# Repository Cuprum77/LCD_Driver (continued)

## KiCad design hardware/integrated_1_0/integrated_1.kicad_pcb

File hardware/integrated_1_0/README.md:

# Integrated Solution rev 1.0

## DO NOT REPRODUCE, CRITICAL ERRORS IN DESIGN

This design features a nasty error where the internal and IO power rails were accidentally swapped. Do not reproduce this design. A new revision is in the works.

## Introduction

This is a PCB that integrates everything needed to drive the display. It is designed to sit on the back of the display without interfering with the display frame. It is specifically designed for the pinout of the newer non-standard displays that have come out of China in the recent years. Specifically those that support the RGB666 interface.

This design utilizes a Spartan 6 FPGA to drive the display. This was chosen over dedicated ASICs due to cost and adaptability. This should allow me to add features such as a splash screen or other custom features that are not possible with a dedicated ASIC.

## Features
- Spartan 6 FPGA [^1]
- DVI Input [^2]
- RP2040 microcontroller
- USB-C [^3] [^4]
- Backlight driver with dimming control
- LCD connector

## LCD Connector

The LCD connector itself is a ZIF 40 pin 0.5mm pitch connector.
The following pinout is in use, with some pins being possible to reconfigure in the FPGA:

TO BE ADDED

[^1]: XC6SLX9-TQG144
[^2]: The DVI input is over a HDMI-like connector. This is due to licensing issues with the HDMI standard that I cannot afford to pay for. Any reference to HDMI in this project is purely for the sake of simplicity and is not meant to imply that this project is HDMI compatible.
[^3]: Does not support PD.
[^4]: Limited to USB 1.1 speeds. This is limited by the RP2040 which handles the USB interface.

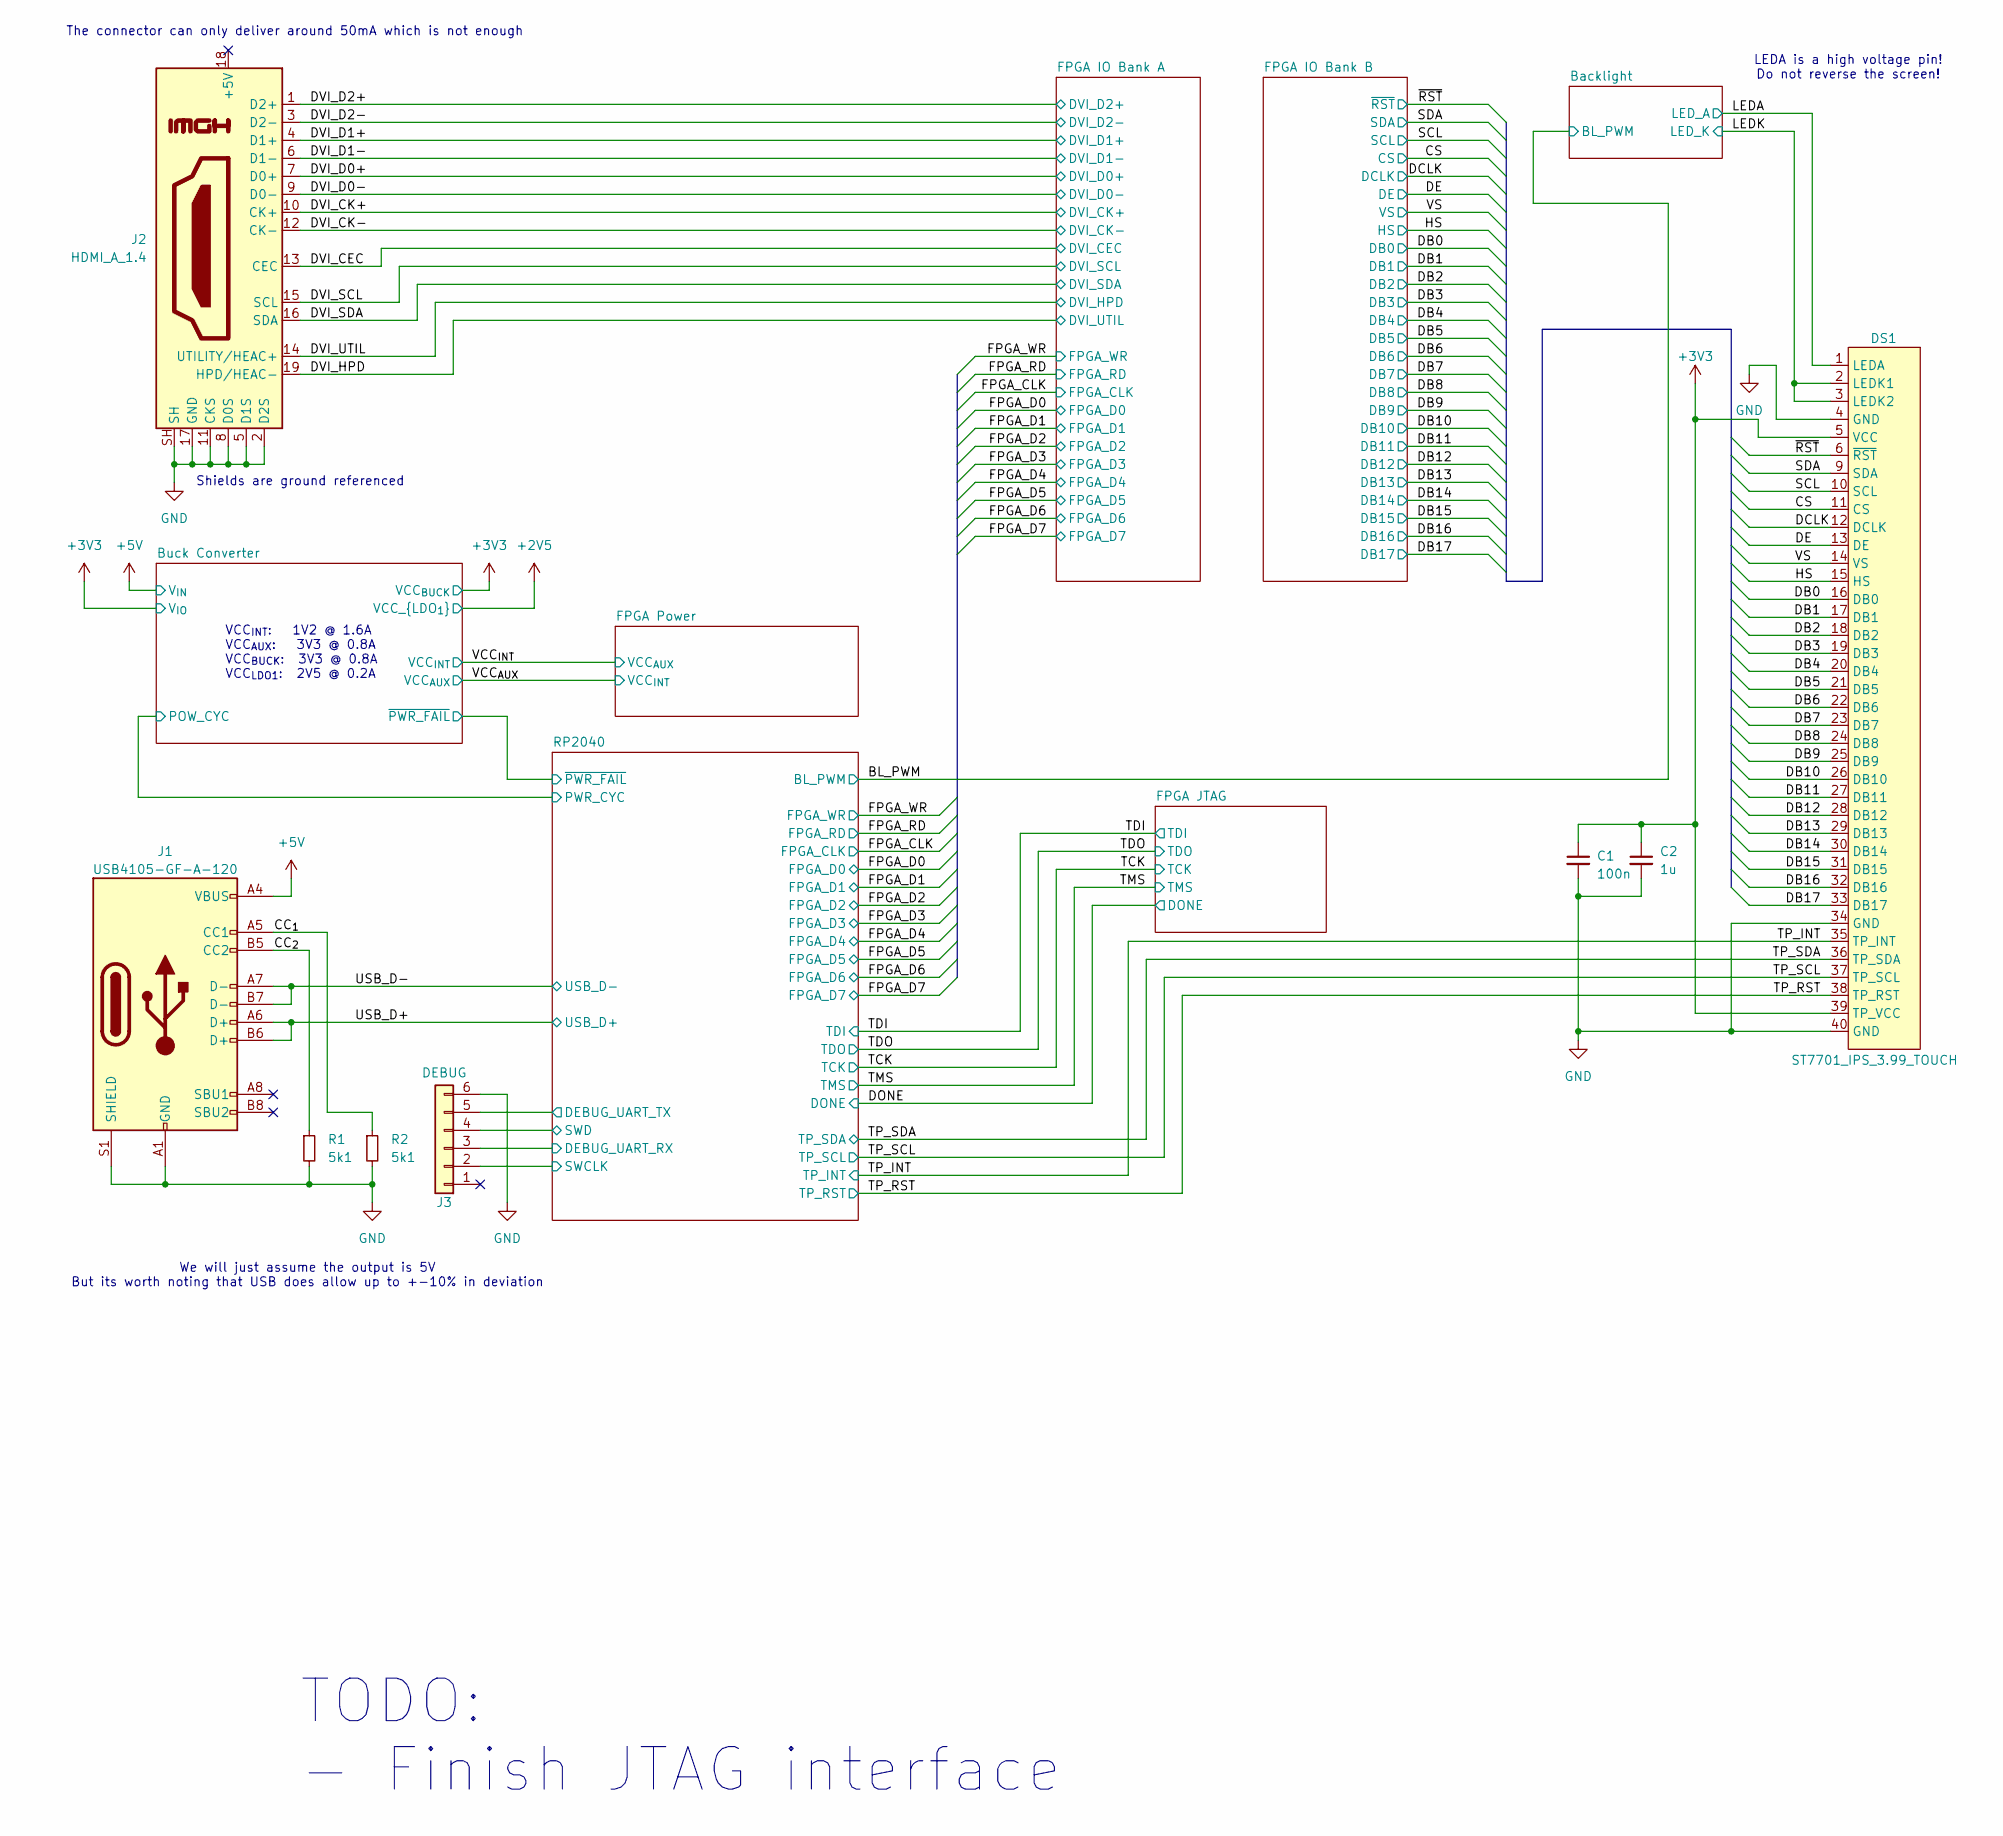
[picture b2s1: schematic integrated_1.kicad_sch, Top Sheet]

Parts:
C1: 100n; C_0402_1005Metric
C2: 1u; C_0402_1005Metric
DS1: ST7701_IPS_3.99_TOUCH; GCT_FFC2B35-40-G_REVA2_INV
J1: USB4105-GF-A-120; CONN_217182-0001_MOL
J2: HDMI_A_1.4; MOLEX_476591102
J3: DEBUG; Paw-Connect_RevB_TC2030-IDC-NL_2x03_P1.27mm_Vertical
R1, R2: 5k1; R_0402_1005Metric

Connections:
+3V3: C1.1, C2.1, DS1.5 (VCC), DS1.39 (TP_VCC); also elsewhere on the board
+5V: J1.A4 (VBUS), J1.A9 (VBUS), J1.B4 (VBUS), J1.B9 (VBUS); also elsewhere on the board
/CC_{1}: J1.A5 (CC1), R2.1
/CC_{2}: J1.B5 (CC2), R1.1
/CS: DS1.11 (CS); also elsewhere on the board
/DB0: DS1.16 (DB0); also elsewhere on the board
/DB1: DS1.17 (DB1); also elsewhere on the board
/DB2: DS1.18 (DB2); also elsewhere on the board
/DB3: DS1.19 (DB3); also elsewhere on the board
/DB4: DS1.20 (DB4); also elsewhere on the board
/DB5: DS1.21 (DB5); also elsewhere on the board
/DB6: DS1.22 (DB6); also elsewhere on the board
/DB7: DS1.23 (DB7); also elsewhere on the board
/DB8: DS1.24 (DB8); also elsewhere on the board
/DB9: DS1.25 (DB9); also elsewhere on the board
/DB10: DS1.26 (DB10); also elsewhere on the board
/DB11: DS1.27 (DB11); also elsewhere on the board
/DB12: DS1.28 (DB12); also elsewhere on the board
/DB13: DS1.29 (DB13); also elsewhere on the board
/DB14: DS1.30 (DB14); also elsewhere on the board
/DB15: DS1.31 (DB15); also elsewhere on the board
/DB16: DS1.32 (DB16); also elsewhere on the board
/DB17: DS1.33 (DB17); also elsewhere on the board
/DCLK: DS1.12 (DCLK); also elsewhere on the board
/DE: DS1.13 (DE); also elsewhere on the board
/DVI_CEC: J2.13 (CEC); also elsewhere on the board
/DVI_CK+: J2.10 (CK+); also elsewhere on the board
/DVI_CK-: J2.12 (CK-); also elsewhere on the board
/DVI_D0+: J2.7 (D0+); also elsewhere on the board
/DVI_D0-: J2.9 (D0-); also elsewhere on the board
/DVI_D1+: J2.4 (D1+); also elsewhere on the board
/DVI_D1-: J2.6 (D1-); also elsewhere on the board
/DVI_D2+: J2.1 (D2+); also elsewhere on the board
/DVI_D2-: J2.3 (D2-); also elsewhere on the board
/DVI_HPD: J2.19 (HPD/HEAC-); also elsewhere on the board
/DVI_SCL: J2.15 (SCL); also elsewhere on the board
/DVI_SDA: J2.16 (SDA); also elsewhere on the board
/DVI_UTIL: J2.14 (UTILITY/HEAC+); also elsewhere on the board
/HS: DS1.15 (HS); also elsewhere on the board
/LEDA: DS1.1 (LEDA); also elsewhere on the board
/LEDK: DS1.2 (LEDK1), DS1.3 (LEDK2); also elsewhere on the board
/RP2040/DEBUG_UART_RX: J3.3; also elsewhere on the board
/RP2040/DEBUG_UART_TX: J3.5; also elsewhere on the board
/RP2040/SWCLK: J3.2; also elsewhere on the board
/RP2040/SWD: J3.4; also elsewhere on the board
/SCL: DS1.10 (SCL); also elsewhere on the board
/SDA: DS1.9 (SDA); also elsewhere on the board
/TP_INT: DS1.35 (TP_INT); also elsewhere on the board
/TP_RST: DS1.38 (TP_RST); also elsewhere on the board
/TP_SCL: DS1.37 (TP_SCL); also elsewhere on the board
/TP_SDA: DS1.36 (TP_SDA); also elsewhere on the board
/USB_D+: J1.A6 (D+), J1.B6 (D+); also elsewhere on the board
/USB_D-: J1.A7 (D-), J1.B7 (D-); also elsewhere on the board
/VS: DS1.14 (VS); also elsewhere on the board
/~RST: DS1.6 (~RST); also elsewhere on the board
GND: C1.2, C2.2, DS1.4 (GND), DS1.34 (GND), DS1.40 (GND), DS1.S1 (GND), DS1.S2 (GND), J1.A1 (GND), J1.A12 (GND), J1.B1 (GND), J1.B12 (GND), J1.S1 (SHIELD), J2.2 (D2S), J2.5 (D1S), J2.8 (D0S), J2.11 (CKS), J2.17 (GND), J2.SH, J2.SH1 (SH), J2.SH2 (SH), J2.SH3 (SH), J3.6, R1.2, R2.2; also elsewhere on the board

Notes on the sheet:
LEDA is a high voltage pin! Do not reverse the screen!
VCC_{INT}: 1V2 @ 1.6A VCC_{AUX}: 3V3 @ 0.8A VCC_{BUCK}: 3V3 @ 0.8A VCC_{LDO1}: 2V5 @ 0.2A
Shields are ground referenced
We will just assume the output is 5V But its worth noting that USB does allow up to +-10% in deviation
TODO: - Finish JTAG interface
The connector can only deliver around 50mA which is not enough

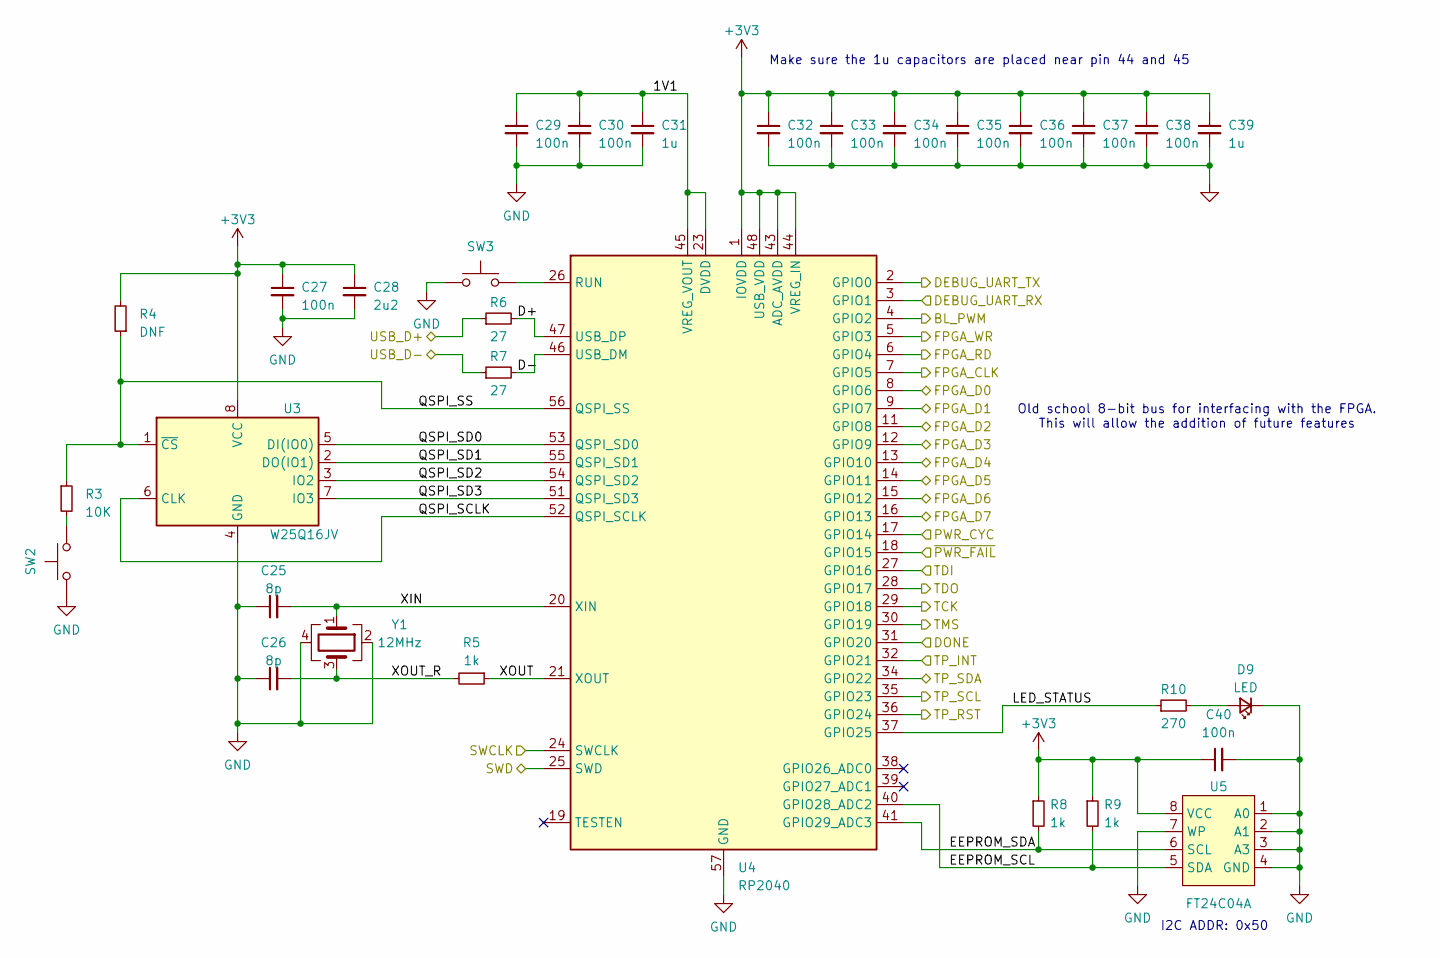
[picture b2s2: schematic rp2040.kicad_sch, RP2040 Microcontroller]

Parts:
C25, C26: 8p; C_0402_1005Metric
C27, C29, C30, C32, C33, C34, C35, C36, C37, C38, C40: 100n; C_0402_1005Metric
C28: 2u2; C_0603_1608Metric
C31, C39: 1u; C_0402_1005Metric
D9: LED; D_0805_2012Metric
R3: 10K; R_0402_1005Metric
R4: DNF; R_0402_1005Metric
R5, R8, R9: 1k; R_0402_1005Metric
R6, R7: 27; R_0402_1005Metric
R10: 270; R_0402_1005Metric
SW2, SW3: DNF; PTS636 SM25J SMTR LFS
U3: W25Q16JV; W25Q16JVUXIQ TR
U4: RP2040; QFN-56-1EP_7x7mm_P0.4mm_EP3.2x3.2mm
U5: FT24C04A; SOIC-8_3.9x4.9mm_P1.27mm
Y1: 12MHz; ECS120836CKMTR3

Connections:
+3V3: C27.1, C28.1, C32.1, C33.1, C34.1, C35.1, C36.1, C37.1, C38.1, C39.1, C40.1, R4.2, R8.1, R9.1, U3.8 (VCC), U4.1 (IOVDD), U4.10 (IOVDD), U4.22 (IOVDD), U4.33 (IOVDD), U4.42 (IOVDD), U4.43 (ADC_AVDD), U4.44 (VREG_IN), U4.48 (USB_VDD), U4.49 (IOVDD), U5.8 (VCC); also elsewhere on the board
/BL_PWM: U4.4 (GPIO2); also elsewhere on the board
/Buck Converter/EN: U4.17 (GPIO14); also elsewhere on the board
/Buck Converter/~PWR_FAIL: U4.18 (GPIO15); also elsewhere on the board
/DONE: U4.31 (GPIO20); also elsewhere on the board
/FPGA_CLK: U4.7 (GPIO5); also elsewhere on the board
/FPGA_D0: U4.8 (GPIO6); also elsewhere on the board
/FPGA_D1: U4.9 (GPIO7); also elsewhere on the board
/FPGA_D2: U4.11 (GPIO8); also elsewhere on the board
/FPGA_D3: U4.12 (GPIO9); also elsewhere on the board
/FPGA_D4: U4.13 (GPIO10); also elsewhere on the board
/FPGA_D5: U4.14 (GPIO11); also elsewhere on the board
/FPGA_D6: U4.15 (GPIO12); also elsewhere on the board
/FPGA_D7: U4.16 (GPIO13); also elsewhere on the board
/FPGA_RD: U4.6 (GPIO4); also elsewhere on the board
/FPGA_WR: U4.5 (GPIO3); also elsewhere on the board
/RP2040/1V1: C29.1, C30.1, C31.1, U4.23 (DVDD), U4.45 (VREG_VOUT), U4.50 (DVDD)
/RP2040/D+: R6.2, U4.47 (USB_DP)
/RP2040/D-: R7.2, U4.46 (USB_DM)
/RP2040/DEBUG_UART_RX: U4.3 (GPIO1); also elsewhere on the board
/RP2040/DEBUG_UART_TX: U4.2 (GPIO0); also elsewhere on the board
/RP2040/EEPROM_SCL: R9.2, U4.40 (GPIO28_ADC2), U5.5 (SDA)
/RP2040/EEPROM_SDA: R8.2, U4.41 (GPIO29_ADC3), U5.6 (SCL)
/RP2040/LED_STATUS: R10.1, U4.37 (GPIO25)
/RP2040/QSPI_SCLK: U3.6 (CLK), U4.52 (QSPI_SCLK)
/RP2040/QSPI_SD0: U3.5 (DI(IO0)), U4.53 (QSPI_SD0)
/RP2040/QSPI_SD1: U3.2 (DO(IO1)), U4.55 (QSPI_SD1)
/RP2040/QSPI_SD2: U3.3 (IO2), U4.54 (QSPI_SD2)
/RP2040/QSPI_SD3: U3.7 (IO3), U4.51 (QSPI_SD3)
/RP2040/QSPI_SS: R3.1, R4.1, U3.1 (~CS), U4.56 (QSPI_SS)
/RP2040/SWCLK: U4.24 (SWCLK); also elsewhere on the board
/RP2040/SWD: U4.25 (SWD); also elsewhere on the board
/RP2040/XIN: C25.2, U4.20 (XIN), Y1.1
/RP2040/XOUT: R5.1, U4.21 (XOUT)
/RP2040/XOUT_R: C26.2, R5.2, Y1.3
/TCK: U4.29 (GPIO18); also elsewhere on the board
/TDI: U4.27 (GPIO16); also elsewhere on the board
/TDO: U4.28 (GPIO17); also elsewhere on the board
/TMS: U4.30 (GPIO19); also elsewhere on the board
/TP_INT: U4.32 (GPIO21); also elsewhere on the board
/TP_RST: U4.36 (GPIO24); also elsewhere on the board
/TP_SCL: U4.35 (GPIO23); also elsewhere on the board
/TP_SDA: U4.34 (GPIO22); also elsewhere on the board
/USB_D+: R6.1; also elsewhere on the board
/USB_D-: R7.1; also elsewhere on the board
GND: C25.1, C26.1, C27.2, C28.2, C29.2, C30.2, C31.2, C32.2, C33.2, C34.2, C35.2, C36.2, C37.2, C38.2, C39.2, C40.2, D9.1 (K), SW2.1, SW3.1, U3.4 (GND), U3.9 (GND), U4.57 (GND), U5.1 (A0), U5.2 (A1), U5.3 (A3), U5.4 (GND), U5.7 (WP), Y1.2, Y1.4; also elsewhere on the board
unnamed: D9.2 (A), R10.2
unnamed: R3.2, SW2.2
unnamed: SW3.2, U4.26 (RUN)

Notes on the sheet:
I2C ADDR: 0x50
Old school 8-bit bus for interfacing with the FPGA. This will allow the addition of future features
Make sure the 1u capacitors are placed near pin 44 and 45

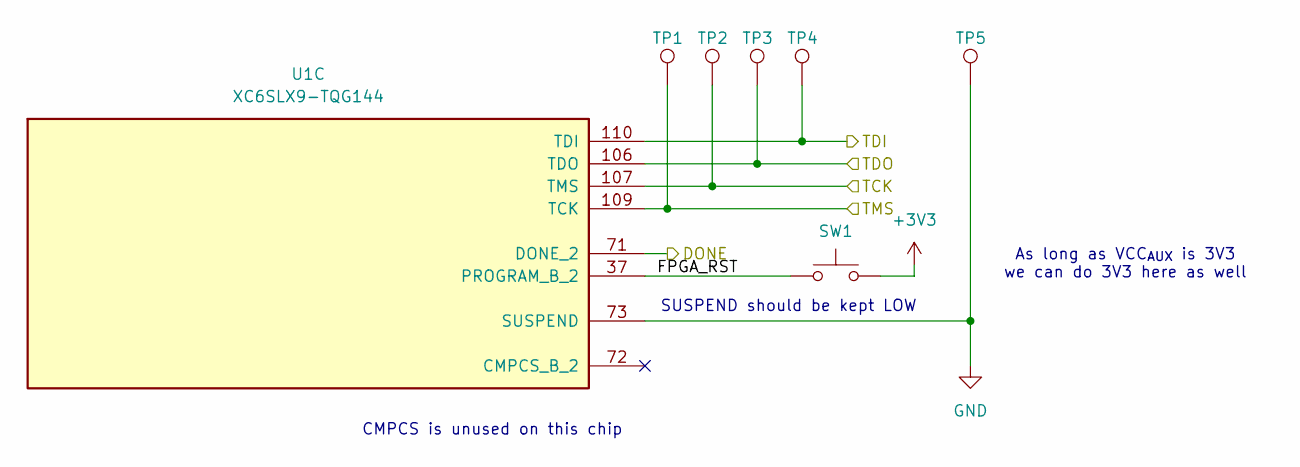
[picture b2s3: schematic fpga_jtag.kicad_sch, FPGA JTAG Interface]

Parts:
SW1: DNF; PTS636 SM25J SMTR LFS
TP1, TP2, TP3, TP4, TP5: TestPoint; TestPoint_Pad_D1.0mm
U1: XC6SLX9-TQG144; TQFP-144_20x20mm_P0.5mm

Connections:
+3V3: SW1.2; also elsewhere on the board
/DONE: U1.71 (DONE_2); also elsewhere on the board
/FPGA JTAG/FPGA_RST: SW1.1, U1.37 (PROGRAM_B_2)
/TCK: TP2.1, U1.107 (TMS); also elsewhere on the board
/TDI: TP4.1, U1.110 (TDI); also elsewhere on the board
/TDO: TP3.1, U1.106 (TDO); also elsewhere on the board
/TMS: TP1.1, U1.109 (TCK); also elsewhere on the board
GND: TP5.1, U1.73 (SUSPEND); also elsewhere on the board

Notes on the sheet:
SUSPEND should be kept LOW
CMPCS is unused on this chip
As long as VCC_{AUX} is 3V3 we can do 3V3 here as well

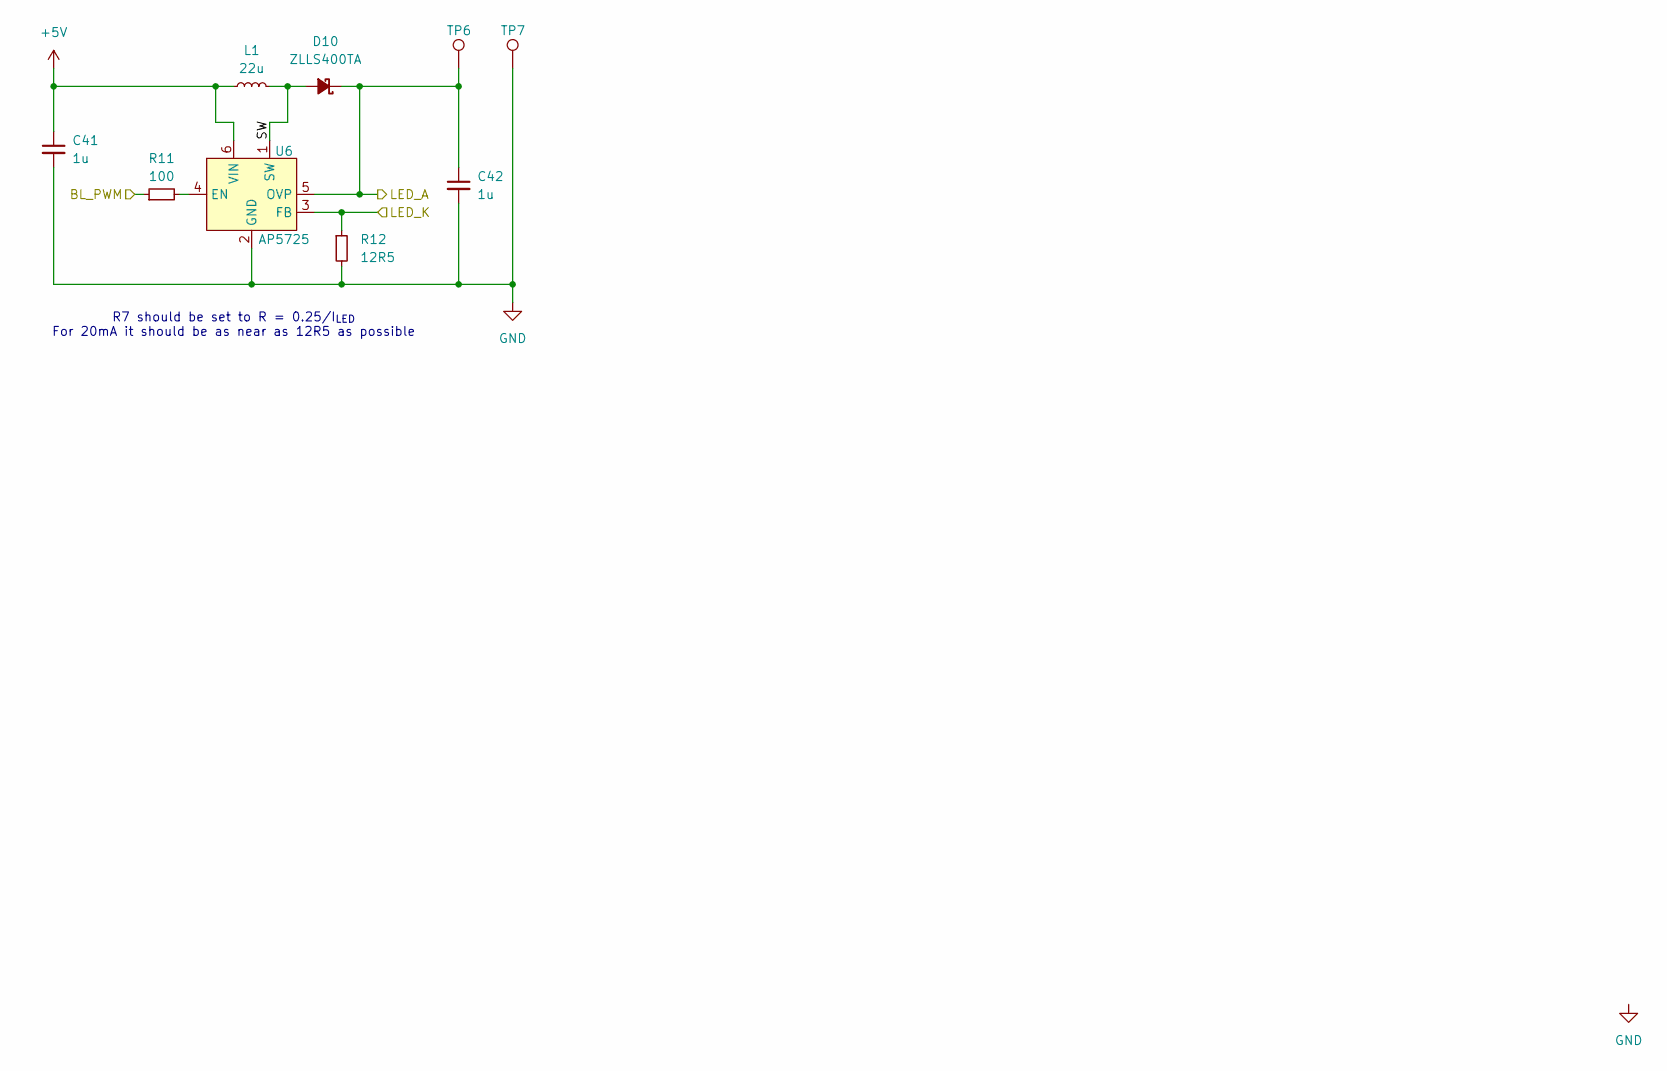
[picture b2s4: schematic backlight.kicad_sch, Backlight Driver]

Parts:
C41: 1u; C_0402_1005Metric
C42: 1u; C_0603_1608Metric
D10: ZLLS400TA; D_SOD-323
L1: 22u; XRNR4012
R11: 100; R_0402_1005Metric
R12: 12R5; R_0603_1608Metric
TP6, TP7: TestPoint; TestPoint_Pad_D1.0mm
U6: AP5725; SOT-23-6

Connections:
+5V: C41.1, L1.1, U6.6 (VIN); also elsewhere on the board
/BL_PWM: R11.1; also elsewhere on the board
/Backlight/SW: D10.2 (A), L1.2, U6.1 (SW)
/LEDA: C42.1, D10.1 (K), TP6.1, U6.5 (OVP); also elsewhere on the board
/LEDK: R12.1, U6.3 (FB); also elsewhere on the board
GND: C41.2, C42.2, R12.2, TP7.1, U6.2 (GND); also elsewhere on the board
unnamed: R11.2, U6.4 (EN)

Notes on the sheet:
R7 should be set to R = 0.25/I_{LED} For 20mA it should be as near as 12R5 as possible

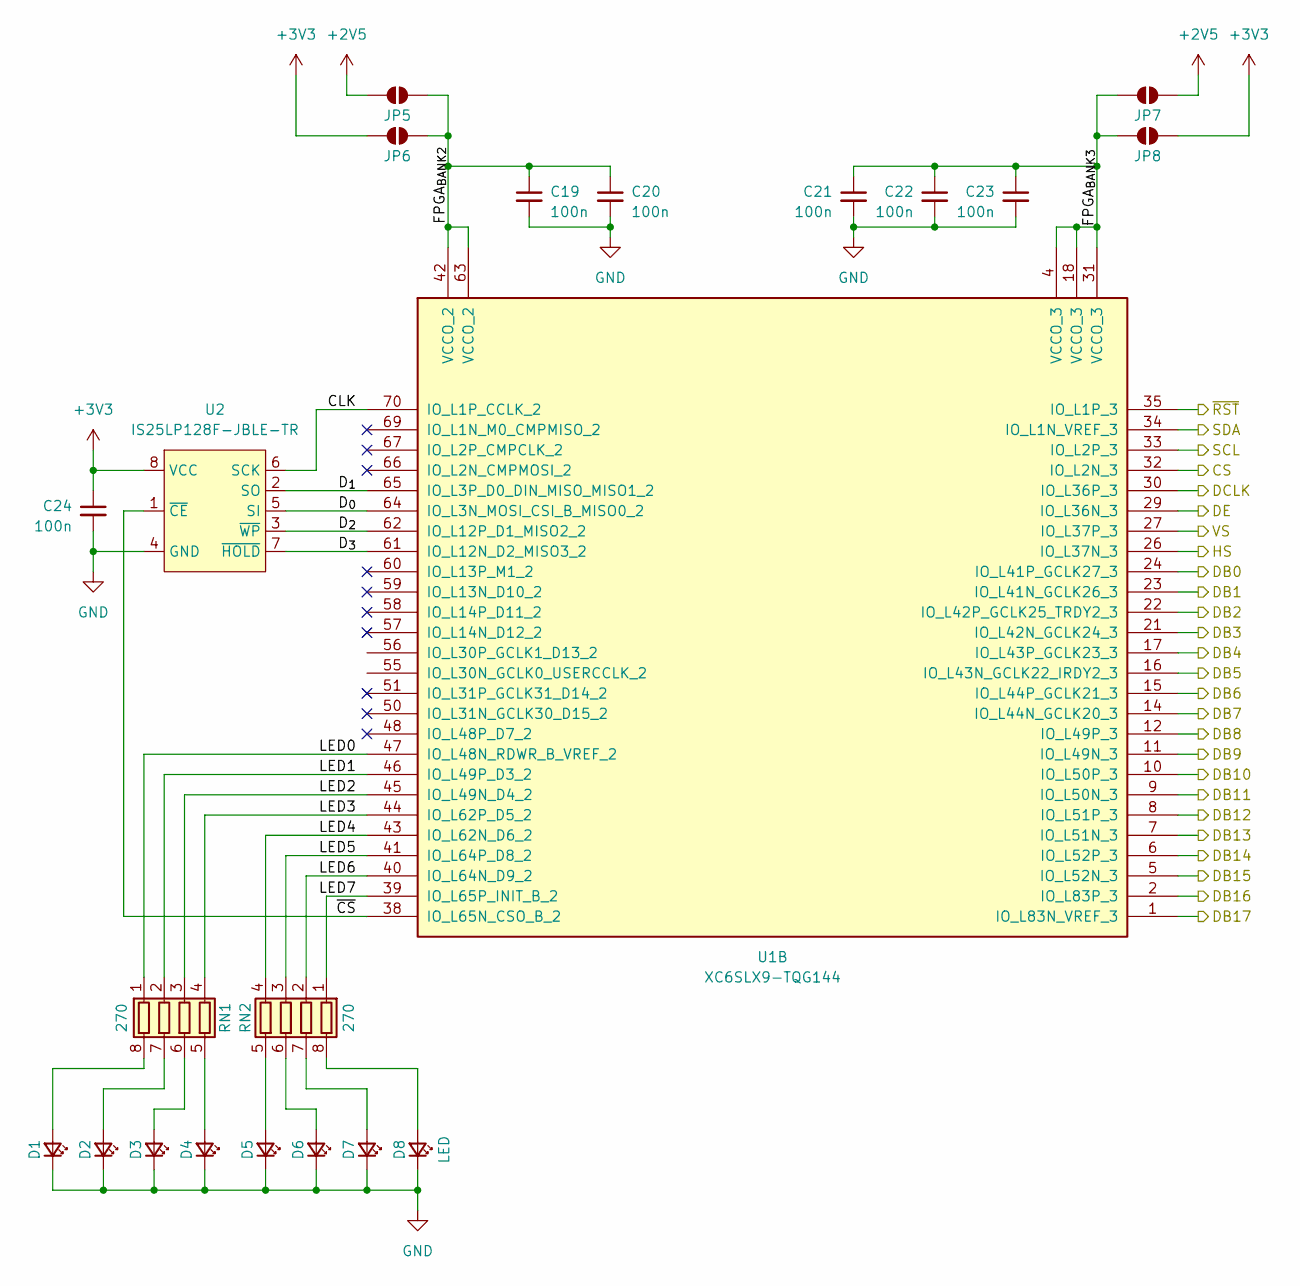
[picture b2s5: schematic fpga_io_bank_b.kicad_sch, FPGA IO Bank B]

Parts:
C19, C20, C21, C22, C23, C24: 100n; C_0402_1005Metric
D1, D2, D3, D4, D5, D6, D7, D8: LED; D_0805_2012Metric
JP5, JP6, JP7, JP8: SolderJumper_2_Open; SolderJumper-2_P1.3mm_Open_RoundedPad1.0x1.5mm
RN1, RN2: 270; C_ARRAY_EXB28V_PAN-L
U1: XC6SLX9-TQG144; TQFP-144_20x20mm_P0.5mm
U2: IS25LP128F-JBLE-TR; SOIC-8_5.275x5.275mm_P1.27mm

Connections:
+2V5: JP5.1 (A), JP7.1 (A); also elsewhere on the board
+3V3: C24.1, JP6.1 (A), JP8.1 (A), U2.8 (VCC); also elsewhere on the board
/CS: U1.32 (IO_L2N_3); also elsewhere on the board
/DB0: U1.24 (IO_L41P_GCLK27_3); also elsewhere on the board
/DB1: U1.23 (IO_L41N_GCLK26_3); also elsewhere on the board
/DB2: U1.22 (IO_L42P_GCLK25_TRDY2_3); also elsewhere on the board
/DB3: U1.21 (IO_L42N_GCLK24_3); also elsewhere on the board
/DB4: U1.17 (IO_L43P_GCLK23_3); also elsewhere on the board
/DB5: U1.16 (IO_L43N_GCLK22_IRDY2_3); also elsewhere on the board
/DB6: U1.15 (IO_L44P_GCLK21_3); also elsewhere on the board
/DB7: U1.14 (IO_L44N_GCLK20_3); also elsewhere on the board
/DB8: U1.12 (IO_L49P_3); also elsewhere on the board
/DB9: U1.11 (IO_L49N_3); also elsewhere on the board
/DB10: U1.10 (IO_L50P_3); also elsewhere on the board
/DB11: U1.9 (IO_L50N_3); also elsewhere on the board
/DB12: U1.8 (IO_L51P_3); also elsewhere on the board
/DB13: U1.7 (IO_L51N_3); also elsewhere on the board
/DB14: U1.6 (IO_L52P_3); also elsewhere on the board
/DB15: U1.5 (IO_L52N_3); also elsewhere on the board
/DB16: U1.2 (IO_L83P_3); also elsewhere on the board
/DB17: U1.1 (IO_L83N_VREF_3); also elsewhere on the board
/DCLK: U1.30 (IO_L36P_3); also elsewhere on the board
/DE: U1.29 (IO_L36N_3); also elsewhere on the board
/FPGA IO Bank B/CLK: U1.70 (IO_L1P_CCLK_2), U2.6 (SCK)
/FPGA IO Bank B/D_{0}: U1.64 (IO_L3N_MOSI_CSI_B_MISO0_2), U2.5 (SI)
/FPGA IO Bank B/D_{1}: U1.65 (IO_L3P_D0_DIN_MISO_MISO1_2), U2.2 (SO)
/FPGA IO Bank B/D_{2}: U1.62 (IO_L12P_D1_MISO2_2), U2.3 (~WP)
/FPGA IO Bank B/D_{3}: U1.61 (IO_L12N_D2_MISO3_2), U2.7 (~HOLD)
/FPGA IO Bank B/FPGA_{BANK2}: C19.1, C20.1, JP5.2 (B), JP6.2 (B), U1.42 (VCCO_2), U1.63 (VCCO_2)
/FPGA IO Bank B/FPGA_{BANK3}: C21.1, C22.1, C23.1, JP7.2 (B), JP8.2 (B), U1.4 (VCCO_3), U1.18 (VCCO_3), U1.31 (VCCO_3)
/FPGA IO Bank B/LED0: RN1.1 (R1.1), U1.47 (IO_L48N_RDWR_B_VREF_2)
/FPGA IO Bank B/LED1: RN1.2 (R2.1), U1.46 (IO_L49P_D3_2)
/FPGA IO Bank B/LED2: RN1.3 (R3.1), U1.45 (IO_L49N_D4_2)
/FPGA IO Bank B/LED3: RN1.4 (R4.1), U1.44 (IO_L62P_D5_2)
/FPGA IO Bank B/LED4: RN2.4 (R4.1), U1.43 (IO_L62N_D6_2)
/FPGA IO Bank B/LED5: RN2.3 (R3.1), U1.41 (IO_L64P_D8_2)
/FPGA IO Bank B/LED6: RN2.2 (R2.1), U1.40 (IO_L64N_D9_2)
/FPGA IO Bank B/LED7: RN2.1 (R1.1), U1.39 (IO_L65P_INIT_B_2)
/FPGA IO Bank B/~CS: U1.38 (IO_L65N_CSO_B_2), U2.1 (~CE)
/HS: U1.26 (IO_L37N_3); also elsewhere on the board
/SCL: U1.33 (IO_L2P_3); also elsewhere on the board
/SDA: U1.34 (IO_L1N_VREF_3); also elsewhere on the board
/VS: U1.27 (IO_L37P_3); also elsewhere on the board
/~RST: U1.35 (IO_L1P_3); also elsewhere on the board
GND: C19.2, C20.2, C21.2, C22.2, C23.2, C24.2, D1.1 (K), D2.1 (K), D3.1 (K), D4.1 (K), D5.1 (K), D6.1 (K), D7.1 (K), D8.1 (K), U2.4 (GND); also elsewhere on the board
unnamed: D1.2 (A), RN1.8 (R1.2)
unnamed: D2.2 (A), RN1.7 (R2.2)
unnamed: D3.2 (A), RN1.6 (R3.2)
unnamed: D4.2 (A), RN1.5 (R4.2)
unnamed: D5.2 (A), RN2.5 (R4.2)
unnamed: D6.2 (A), RN2.6 (R3.2)
unnamed: D7.2 (A), RN2.7 (R2.2)
unnamed: D8.2 (A), RN2.8 (R1.2)

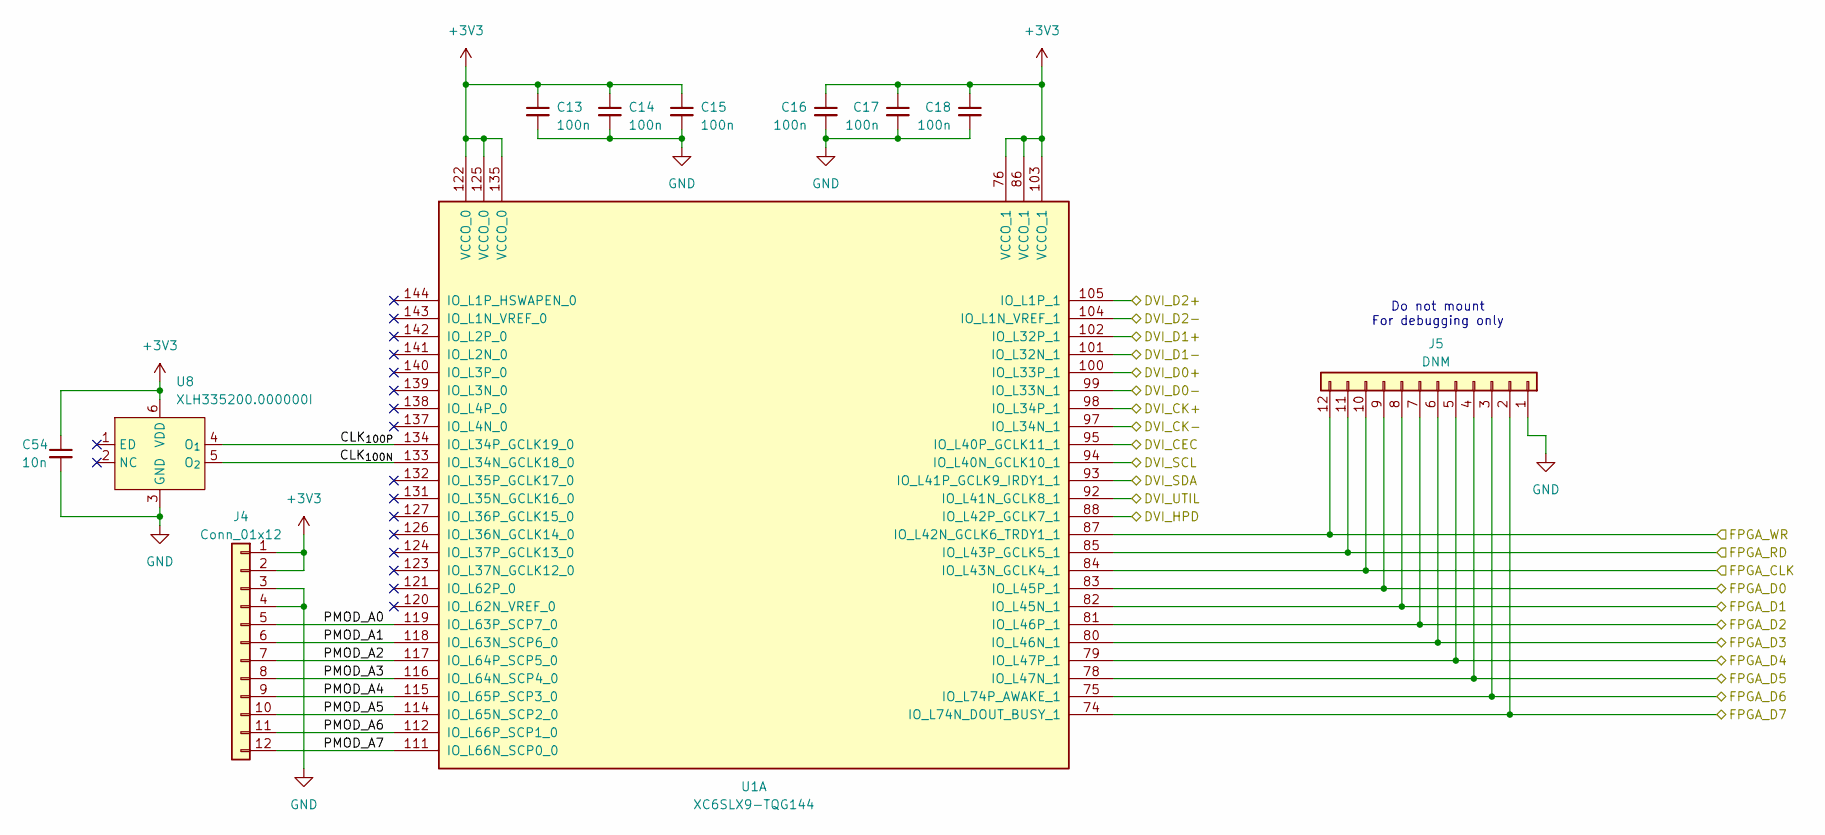
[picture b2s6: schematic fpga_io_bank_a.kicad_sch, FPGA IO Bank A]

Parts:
C13, C14, C15, C16, C17, C18: 100n; C_0402_1005Metric
C54: 10n; C_0402_1005Metric
J4: Conn_01x12; PinHeader_2x06_P1.00mm_Vertical_SMD
J5: DNM; PinHeader_2x06_P1.00mm_Vertical_SMD
U1: XC6SLX9-TQG144; TQFP-144_20x20mm_P0.5mm
U8: XLH335200.000000I

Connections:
+3V3: C13.1, C14.1, C15.1, C16.1, C17.1, C18.1, C54.1, J4.1, J4.2, U1.76 (VCCO_1), U1.86 (VCCO_1), U1.103 (VCCO_1), U1.122 (VCCO_0), U1.125 (VCCO_0), U1.135 (VCCO_0), U8.6 (VDD); also elsewhere on the board
/DVI_CEC: U1.95 (IO_L40P_GCLK11_1); also elsewhere on the board
/DVI_CK+: U1.98 (IO_L34P_1); also elsewhere on the board
/DVI_CK-: U1.97 (IO_L34N_1); also elsewhere on the board
/DVI_D0+: U1.100 (IO_L33P_1); also elsewhere on the board
/DVI_D0-: U1.99 (IO_L33N_1); also elsewhere on the board
/DVI_D1+: U1.102 (IO_L32P_1); also elsewhere on the board
/DVI_D1-: U1.101 (IO_L32N_1); also elsewhere on the board
/DVI_D2+: U1.105 (IO_L1P_1); also elsewhere on the board
/DVI_D2-: U1.104 (IO_L1N_VREF_1); also elsewhere on the board
/DVI_HPD: U1.92 (IO_L41N_GCLK8_1); also elsewhere on the board
/DVI_SCL: U1.94 (IO_L40N_GCLK10_1); also elsewhere on the board
/DVI_SDA: U1.93 (IO_L41P_GCLK9_IRDY1_1); also elsewhere on the board
/DVI_UTIL: U1.88 (IO_L42P_GCLK7_1); also elsewhere on the board
/FPGA IO Bank A/CLK_{100N}: U1.133 (IO_L34N_GCLK18_0), U8.5 (O_{2})
/FPGA IO Bank A/CLK_{100P}: U1.134 (IO_L34P_GCLK19_0), U8.4 (O_{1})
/FPGA IO Bank A/PMOD_A0: J4.5, U1.119 (IO_L63P_SCP7_0)
/FPGA IO Bank A/PMOD_A1: J4.6, U1.118 (IO_L63N_SCP6_0)
/FPGA IO Bank A/PMOD_A2: J4.7, U1.117 (IO_L64P_SCP5_0)
/FPGA IO Bank A/PMOD_A3: J4.8, U1.116 (IO_L64N_SCP4_0)
/FPGA IO Bank A/PMOD_A4: J4.9, U1.115 (IO_L65P_SCP3_0)
/FPGA IO Bank A/PMOD_A5: J4.10, U1.114 (IO_L65N_SCP2_0)
/FPGA IO Bank A/PMOD_A6: J4.11, U1.112 (IO_L66P_SCP1_0)
/FPGA IO Bank A/PMOD_A7: J4.12, U1.111 (IO_L66N_SCP0_0)
/FPGA_CLK: J5.10, U1.84 (IO_L43N_GCLK4_1); also elsewhere on the board
/FPGA_D0: J5.9, U1.83 (IO_L45P_1); also elsewhere on the board
/FPGA_D1: J5.8, U1.82 (IO_L45N_1); also elsewhere on the board
/FPGA_D2: J5.7, U1.81 (IO_L46P_1); also elsewhere on the board
/FPGA_D3: J5.6, U1.80 (IO_L46N_1); also elsewhere on the board
/FPGA_D4: J5.5, U1.79 (IO_L47P_1); also elsewhere on the board
/FPGA_D5: J5.4, U1.78 (IO_L47N_1); also elsewhere on the board
/FPGA_D6: J5.3, U1.75 (IO_L74P_AWAKE_1); also elsewhere on the board
/FPGA_D7: J5.2, U1.74 (IO_L74N_DOUT_BUSY_1); also elsewhere on the board
/FPGA_RD: J5.11, U1.85 (IO_L43P_GCLK5_1); also elsewhere on the board
/FPGA_WR: J5.12, U1.87 (IO_L42N_GCLK6_TRDY1_1); also elsewhere on the board
GND: C13.2, C14.2, C15.2, C16.2, C17.2, C18.2, C54.2, J4.3, J4.4, J5.1, U8.3 (GND); also elsewhere on the board

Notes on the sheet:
Do not mount For debugging only
